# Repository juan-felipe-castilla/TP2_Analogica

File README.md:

# Laboratorio 2: Amplificador BJT Multietapa

Repositorio del **Laboratorio 2** para la asignatura de Electrónica. El objetivo de este proyecto es diseñar, simular, implementar en PCB y caracterizar experimentalmente un amplificador en cascada basado en transistores BJT.

---

## 👥 Integrantes (Grupo N°)
- **[Castilla Juan Felipe]** 
- **[Agustin Eduardo Dalmazzo]**
- **[Julian Lopez Bernal]** 

---

## 🎯 Especificaciones de Diseño

| Parámetro | Valor Requerido |
| :--- | :--- |
| **Ganancia de Tensión de Transf. ($G_T$)** | $> 75$ |
| **Impedancia de Entrada ($Z_{in}$)** | $> 350\text{ k}\Omega$ |
| **Impedancia de Salida ($Z_o$)** | $8\Omega \pm 5\%$ |

---

## 🛠️ Estructura del Repositorio

```text
.
├── docs/                   # Guías, hojas de datos (datasheets) e informe final
│   └── Informe_Laboratorio_2.pdf
├── design/                 # Cálculos teóricos, hojas de cálculo o notebooks
├── simulation/             # Archivos de simulación (SPICE / LTspice / Altium)
│   ├── bias_point/         # Análisis del punto de operación (OP)
│   ├── ac_analysis/        # Respuestas en frecuencia (AC)
│   └── transient/          # Análisis temporal, ruido y THD (TRAN / NOISE / FFT)
├── pcb/                    # Archivos de diseño de circuito impreso (KiCad / Altium)
│   ├── schematics/
│   ├── layout/
│   └── gerbers/
└── README.md

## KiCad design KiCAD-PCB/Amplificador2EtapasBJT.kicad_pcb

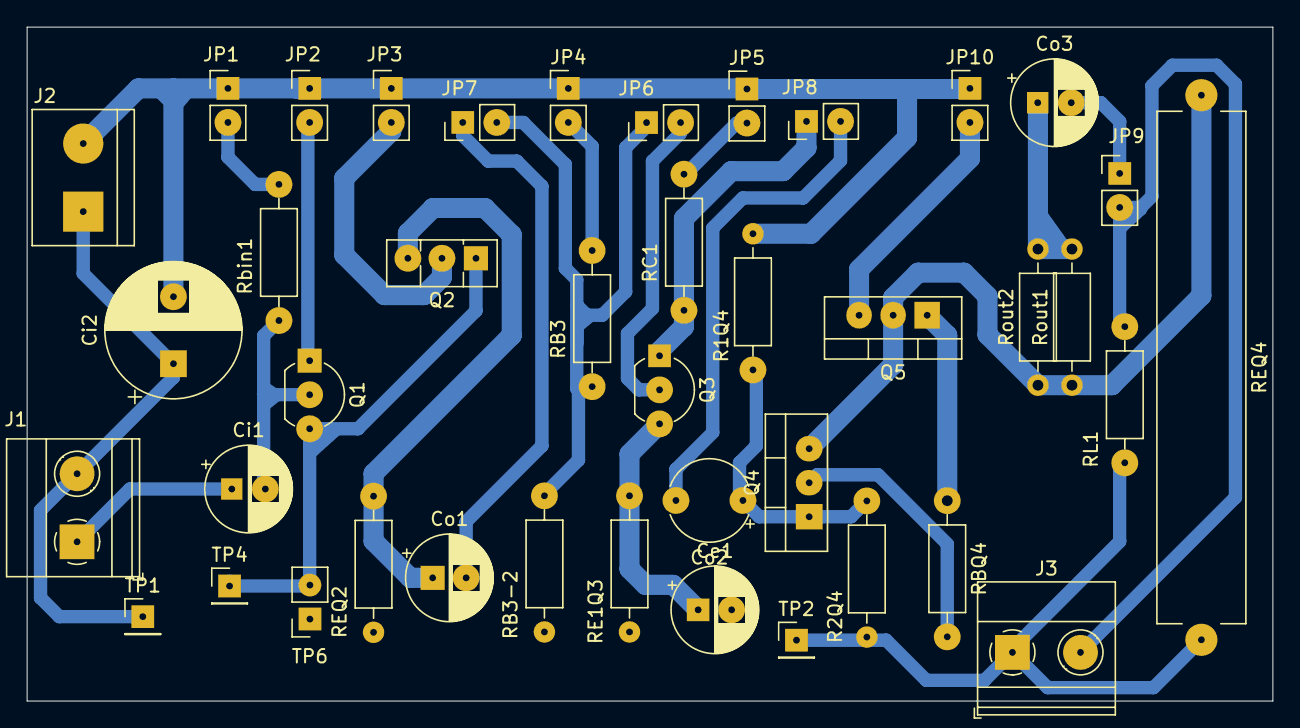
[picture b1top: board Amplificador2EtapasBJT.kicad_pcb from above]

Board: 2 copper layers, 93.0 x 50.3 mm, 41 parts (0 on the bottom side), 24 nets.

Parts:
Ce1: 33uF; CP_Radial_D6.3mm_P2.50mm
Ci1: 10uF; CP_Radial_D6.3mm_P2.50mm
Ci2: 10uF; CP_Radial_D10.0mm_P5.00mm
Co1: 10uF; CP_Radial_D6.3mm_P2.50mm
Co2: 10uF; CP_Radial_Tantal_D6.0mm_P5.00mm
Co3: 1000uF; CP_Radial_D6.3mm_P2.50mm
J1: Vin; TerminalBlock_Phoenix_MKDS-1,5-2-5.08_1x02_P5.08mm_Horizont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
J2: CC; TerminalBlock_bornier-2_P5.08mm
J3: Vout; TerminalBlock_Phoenix_MKDS-1,5-2-5.08_1x02_P5.08mm_Horizont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
JP1: RbQ1; PinHeader_1x02_P2.54mm_Vertical
JP2: C-Q1; PinHeader_1x02_P2.54mm_Vertical
JP3: C-Q2; PinHeader_1x02_P2.54mm_Vertical
JP4: Div-Q3; PinHeader_1x02_P2.54mm_Vertical
JP5: C-Q3; PinHeader_1x02_P2.54mm_Vertical
JP6: B-Q3; PinHeader_1x02_P2.54mm_Vertical
JP7: FinEtapa1; PinHeader_1x02_P2.54mm_Vertical
JP8: FinEtapa2; PinHeader_1x02_P2.54mm_Vertical
JP9: ConRL; PinHeader_1x02_P2.54mm_Vertical
JP10: C-Q5; PinHeader_1x02_P2.54mm_Vertical
Q1: BC546 B NPN; TO-92_Inline_Wide
Q2: BD 139NPN; TO-126-3_Vertical
Q3: NPN; TO-92_Inline_Wide
Q4: NPN; TO-220-3_Vertical
Q5: PNP; TO-220-3_Vertical
R1Q4: 47k; R_Axial_DIN0207_L6.3mm_D2.5mm_P10.16mm_Horizontal
R2Q4: 100k; R_Axial_DIN0207_L6.3mm_D2.5mm_P10.16mm_Horizontal
RB3: 120k; R_Axial_DIN0207_L6.3mm_D2.5mm_P10.16mm_Horizontal
RB3-2: 27k; R_Axial_DIN0207_L6.3mm_D2.5mm_P10.16mm_Horizontal
RBQ4: 100; R_Axial_DIN0207_L6.3mm_D2.5mm_P10.16mm_Horizontal
RC1: 6.8k; R_Axial_DIN0207_L6.3mm_D2.5mm_P10.16mm_Horizontal
RE1Q3: 1.2k; R_Axial_DIN0207_L6.3mm_D2.5mm_P10.16mm_Horizontal
REQ2: 47; R_Axial_DIN0207_L6.3mm_D2.5mm_P10.16mm_Horizontal
REQ4: 10; R_Axial_Power_L38.0mm_W6.4mm_P40.64mm
RL1: 8; R_Axial_DIN0207_L6.3mm_D2.5mm_P10.16mm_Horizontal
Rbin1: 1M; R_Axial_DIN0207_L6.3mm_D2.5mm_P10.16mm_Horizontal
Rout1: 10; R_Axial_DIN0207_L6.3mm_D2.5mm_P10.16mm_Horizontal
Rout2: 15; R_Axial_DIN0207_L6.3mm_D2.5mm_P10.16mm_Horizontal
TP1, TP2: TPFrec; PinHeader_1x01_P2.54mm_Vertical
TP4: TPB-Q2; PinHeader_1x01_P2.54mm_Vertical
TP6: TPB2E1; PinSocket_1x02_P2.54mm_Vertical

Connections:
Earth: Ce1.2, Ci2.1, J1.1, J2.1, J3.1, R2Q4.1, RB3-2.2, RE1Q3.2, REQ2.2, REQ4.2, RL1.2, TP1.1, TP2.1, TP6.1
unnamed: Co3.1, Rout1.2, Rout2.2
unnamed: Ci1.1, J1.2
unnamed: Ci2.2, J2.2, JP1.1 (A), JP2.1 (A), JP3.1 (A), JP4.1 (A), JP5.1 (A), JP10.1 (A), R1Q4.2
unnamed: J3.2, JP9.2 (B), RL1.1
unnamed: JP1.2 (B), Rbin1.1
unnamed: JP2.2 (B), Q1.1 (C)
unnamed: JP3.2 (B), Q2.1 (C)
unnamed: JP4.2 (B), RB3.1
unnamed: JP5.2 (B), RC1.1
unnamed: JP6.1 (A), JP7.2 (B), RB3.2, RB3-2.1
unnamed: JP6.2 (B), Q3.2 (B)
unnamed: Co1.2, JP7.1 (A)
unnamed: Co2.2, JP8.2 (B), Q4.2 (B), R1Q4.1, R2Q4.2
unnamed: Co3.2, JP9.1 (A)
unnamed: JP10.2 (B), Q5.3 (E)
unnamed: Ci1.2, Q1.2 (B), Rbin1.2
unnamed: Q1.3 (E), Q2.2 (B), TP4.1, TP6.2
unnamed: Co1.1, Q2.3 (E), REQ2.1
unnamed: Q3.1 (C), RC1.2
unnamed: Ce1.1, Q3.3 (E), RE1Q3.1
unnamed: Q4.1 (C), RBQ4.2
unnamed: Q4.3 (E), Q5.1 (C), REQ4.1, Rout1.1, Rout2.1
unnamed: Q5.2 (B), RBQ4.1
